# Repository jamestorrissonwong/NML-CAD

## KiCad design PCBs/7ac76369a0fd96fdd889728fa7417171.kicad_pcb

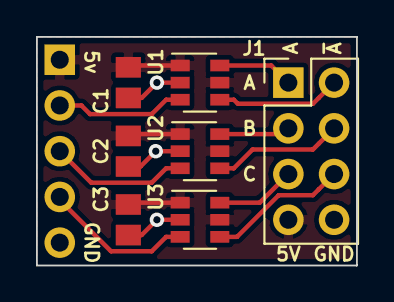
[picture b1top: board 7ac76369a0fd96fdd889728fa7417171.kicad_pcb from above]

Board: 2 copper layers, 17.8 x 12.7 mm, 8 parts (1 on the bottom side), 11 nets.

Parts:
C1, C2, C3: 100nF; C_0805_2012Metric
J1: Conn_02x04_Odd_Even; PinHeader_2x04_P2.54mm_Vertical
J2: ODrive Connector; PinHeader_1x05_P2.54mm_Vertical
U1, U2, U3: MAX3284E; SOT-23-6

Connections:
+5V: C1.1, C2.1, C3.1, J1.7, J2.1, U1.1, U1.5, U2.1, U2.5, U3.1, U3.5
/A: J1.1, U1.6
/A_Out: J2.2, U1.3
/B: J1.3, U2.6
/B_Out: J2.3, U2.3
/Z: J1.5, U3.6
/Z_Out: J2.4, U3.3
/~A: J1.2, U1.4
/~B: J1.4, U2.4
/~Z: J1.6, U3.4
GND: C1.2, C2.2, C3.2, J1.8, J2.5, U1.2, U2.2, U3.2

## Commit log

2021-07-27 7/27
2021-08-02 8/2/21
2021-08-03 8/3/21
2021-08-03 8/3/21 v2
2021-08-06 8/6/21
2021-08-28 8/28/21
2021-12-15 XPS 12/15
2021-12-19 121821
2021-12-19 max manip mods
2021-12-23 DT 12-23
2022-01-06 DT 1/5/22
2022-02-23 2/6/22 -- before icts rail updates + 2/22/22 ICTS
2022-06-04 2022-06-04
2022-06-11 2022-06-11
2022-08-11 08/10/22
